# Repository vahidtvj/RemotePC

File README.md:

# RemotePC
> An ESP8266 powered PC addon card to remotely power it on using mqtt

## How to Build
You need a server to run your mqtt broker on. You can skip this and use a ready made service. The default setup runs MQTT over websocket with TLS. The PCB is designed to be printable at home ( All vias are open and accessible. THT components are soldered only from the other side. )
- Server
  - Get a server. A container even with host routing (no dedicated IP) would do
  - Generate passwords for your mqtt client and the ESP store them in `passwd`
  - After running the server make sure it works with the given test scripts

- ESP board
  - Create a secrets file and also fill in your servers CA certificate in `main.h`
  - For programming use the 3 test points. Hold the button before plugging power to set ESP to bootloader mode
  - Flash the ESP. You should be able to test it with the led command (will flash the on board LED)

The board is designed to be powered from PC 5V Standby. You can plug in your power and reset buttons to the header pins on the board

### Testing

Inside the `test` folder, JavaScript files can be run with Node.js to subscribe to or publish MQTT topics as tests.

### MQTT Topics

- `/pc_led`  
  Payload: `"on"` or `"off"`  
  Controls the onboard LED (on = LED ON, off = LED OFF).

- `/pc`    
  - `"get"`: Publishes current PC power state on `/pc_state` (`"on"` or `"off"`).  
  - `"power"`: Toggles PC power by pulsing the power pin.  
  - `"reset"`: Pulses the reset pin to reset the PC.

## License
[MIT](https://github.com/vahidtvj/RemotePC/blob/master/LICENCE) © [vahidtvj](https://github.com/vahidtvj)

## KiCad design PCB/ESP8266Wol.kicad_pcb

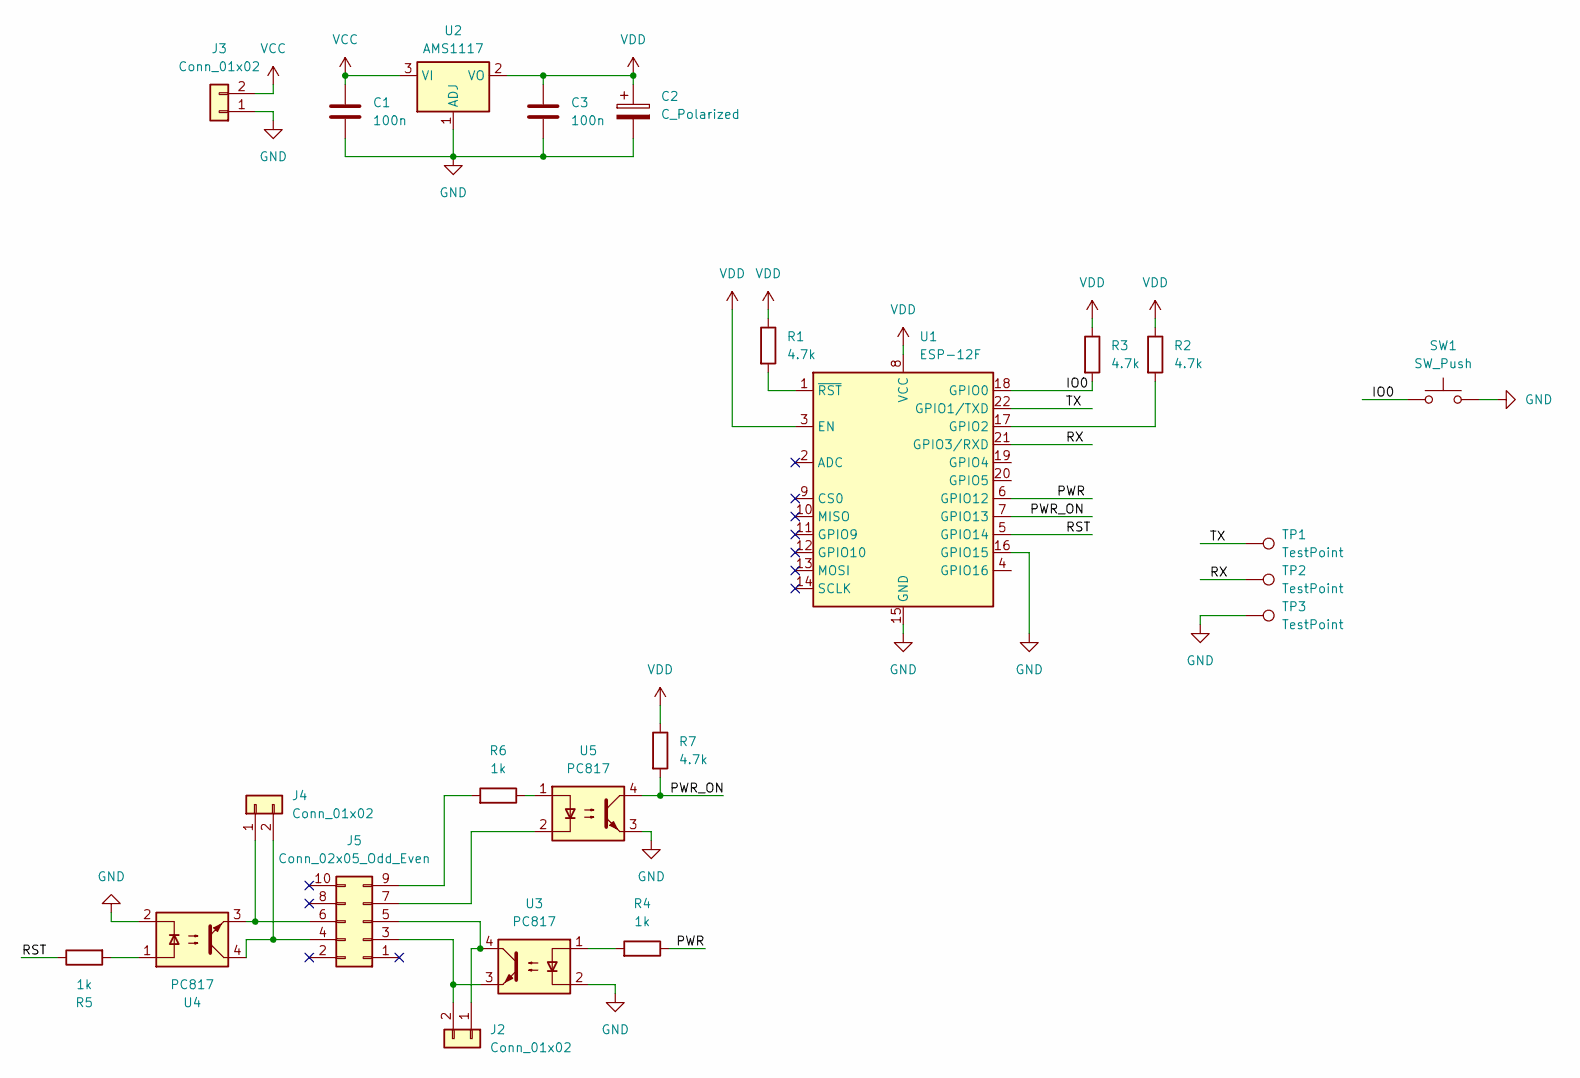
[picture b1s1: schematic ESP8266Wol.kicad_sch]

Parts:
C1, C3: 100n; C_0805_2012Metric
C2: C_Polarized; C_Elec_5x5.4
J2, J4: Conn_01x02; PinHeader_1x02_P2.54mm_Vertical
J3: Conn_01x02; JST_XH_B2B-XH-A_1x02_P2.50mm_Vertical
J5: Conn_02x05_Odd_Even; PinSocket_2x05_P2.54mm_Horizontal
R1, R2, R3, R7: 4.7k; R_0805_2012Metric
R4, R5, R6: 1k; R_0805_2012Metric
SW1: SW_Push; SW_Push_1P1T_XKB_TS-1187A
TP1, TP2: TestPoint; TestPoint_Pad_D1.5mm
TP3: TestPoint; TestPoint_Pad_1.5x1.5mm
U1: ESP-12F; ESP-12E
U2: AMS1117; SOT-223-3_TabPin2
U3, U4, U5: PC817; DIP-4_W7.62mm

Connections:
/IO0: R3.2, SW1.1, U1.18 (GPIO0)
/PWR: R4.1, U1.6 (GPIO12)
/PWR_ON: R7.2, U1.7 (GPIO13), U5.4
/RST: R5.1, U1.5 (GPIO14)
/RX: TP2.1, U1.21 (GPIO3/RXD)
/TX: TP1.1, U1.22 (GPIO1/TXD)
GND: C1.2, C2.2, C3.2, J3.1, SW1.2, TP3.1, U1.15 (GND), U1.16 (GPIO15), U2.1 (ADJ), U3.2, U4.2, U5.3
unnamed: J2.1, J5.5, U3.4
unnamed: J2.2, J5.3, U3.3
unnamed: J4.1, J5.6, U4.3
unnamed: J4.2, J5.4, U4.4
unnamed: J5.7, U5.2
unnamed: J5.9, R6.2
unnamed: R4.2, U3.1
unnamed: R5.2, U4.1
unnamed: R6.1, U5.1
unnamed: R2.2, U1.17 (GPIO2)
unnamed: R1.2, U1.1 (~RST)
VCC: C1.1, J3.2, U2.3 (VI)
VDD: C2.1, C3.1, R1.1, R2.1, R3.1, R7.1, U1.3 (EN), U1.8 (VCC), U2.2 (VO)

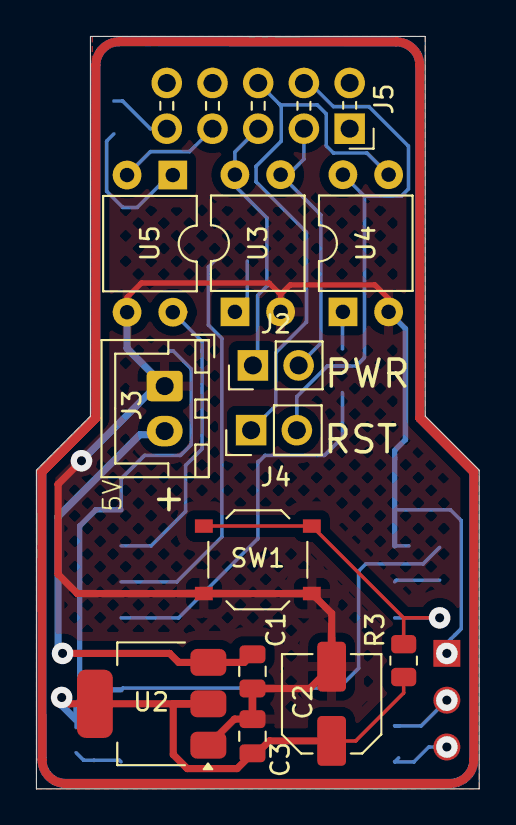
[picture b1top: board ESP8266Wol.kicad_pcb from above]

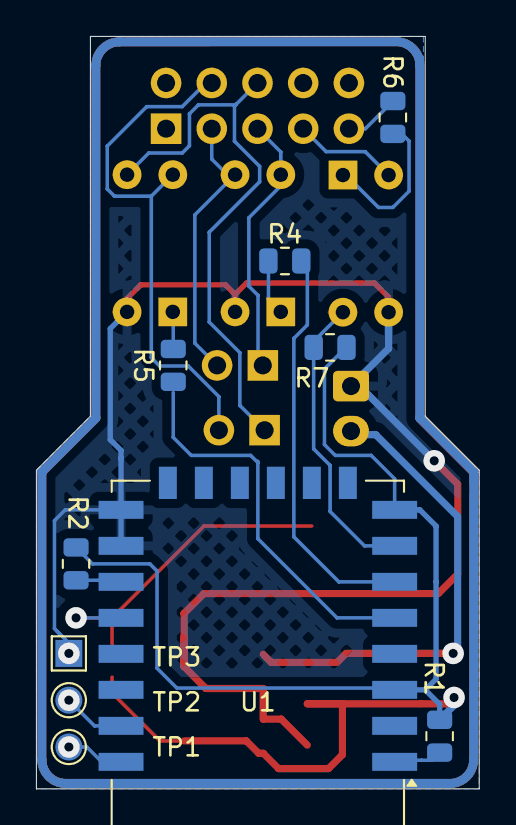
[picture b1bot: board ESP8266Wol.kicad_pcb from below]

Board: 2 copper layers, 24.6 x 41.8 mm, 23 parts (10 on the bottom side), 20 nets.

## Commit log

2025-06-07 add readme
2025-06-07 update silkscreen
